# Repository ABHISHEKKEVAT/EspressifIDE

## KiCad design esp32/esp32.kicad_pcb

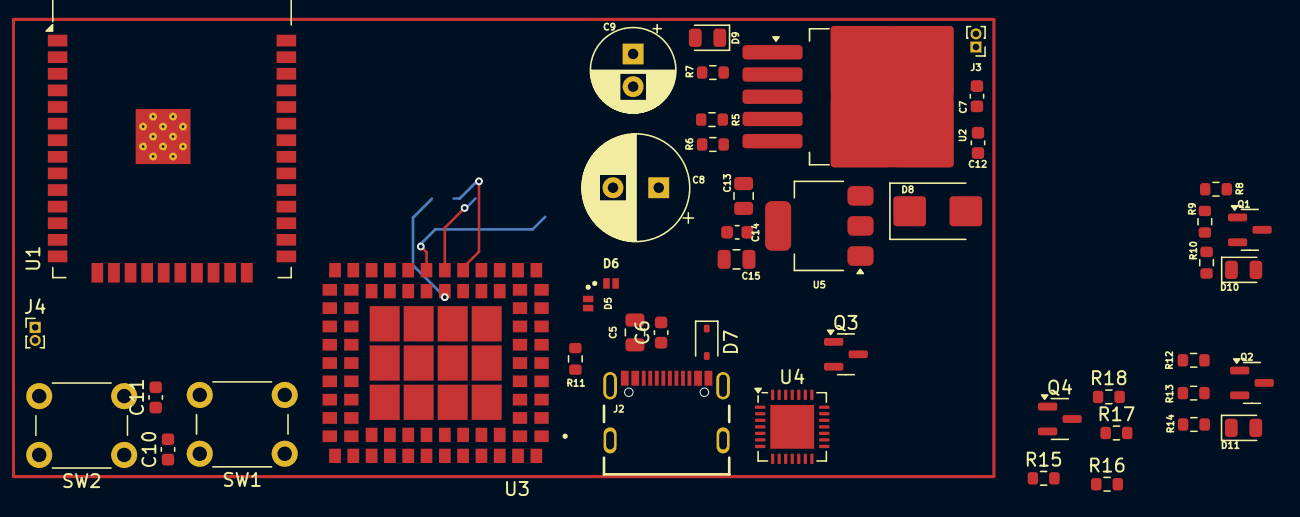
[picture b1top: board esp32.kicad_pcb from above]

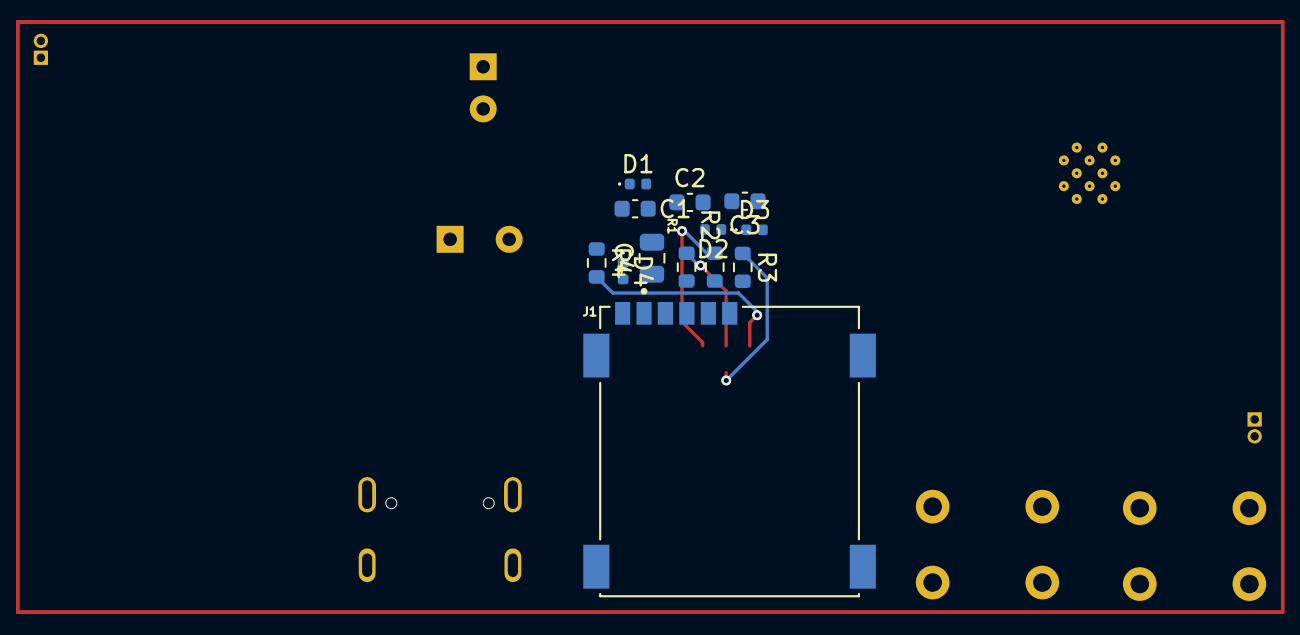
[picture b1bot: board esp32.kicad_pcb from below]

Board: 2 copper layers, 59 parts (13 on the bottom side), 44 nets.

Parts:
C1, C2, C3: 8.2p; C_0603_1608Metric
C4, C5: 1u; C_0805_2012Metric
C6: 22p; C_0603_1608Metric
C7, C12, C14: 100n; C_0603_1608Metric
C8: 100u; CP_Radial_D8.0mm_P3.50mm
C9: 22u; CP_Radial_D6.3mm_P2.50mm
C10, C11: 0.1UF/50V; C_0603_1608Metric
C13, C15: 10u; C_0805_2012Metric
D1, D2, D3, D4: SPD9103W; D_0402_1005Metric
D5, D6: AQ3045-01ETG; DIO_PESD5V0S1UL,315
D7: PESD24VL1BA; D_SOD-323
D8: SS34; D_SMB
D9: PWR; LED_0805_2012Metric
D10: NET; LED_0805_2012Metric
D11: STATUS; LED_0805_2012Metric
J1: SIM7200-6-0-18-00-X_REVA; CUI_MSIM-2-A
J2: USB4105-GF-A; GCT_USB4105-GF-A
J3: PWR; PinHeader_1x02_P1.00mm_Vertical
J4: Conn_01x02; PinHeader_1x02_P1.00mm_Vertical
Q1, Q2, Q3, Q4: BC847; SOT-23
R1, R2, R3: 20R; R_0603_1608Metric
R4, R8, R12: 4.7K; R_0603_1608Metric
R5: 10K; R_0603_1608Metric
R6: 4K7; R_0603_1608Metric
R7, R10, R14: 470R; R_0603_1608Metric
R9, R13: 47K; R_0603_1608Metric
R11: 1K5; R_0603_1608Metric
R15, R16, R17, R18: 0R; R_0603_1608Metric
SW1, SW2: SW_Push; SW_PUSH_6mm_H5mm
U1: ESP32-WROOM-32
U2: MIC29302WU; TO-263-5_TabPin3
U3: SIM800L; MODULE_SIM800L
U4: CP2102N-Axx-xQFN28; QFN-28-1EP_5x5mm_P0.5mm_EP3.35x3.35mm
U5: LM1117MP-3.3; SOT-223-3_TabPin2

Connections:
+3.3V: C14.1, C15.1, U1.2 (VDD), U5.2 (VO)
/esp32/DTR: Q4.3 (C), R17.1, U4.28 (~DTR)
/esp32/EN: Q3.3 (C), U1.3 (EN)
/esp32/IO0: Q4.2 (E), U1.25 (IO0)
/esp32/RTS: Q3.2 (E), R18.1, U4.24 (~RTS)
/esp32/RXD: R15.1, U4.25 (RXD)
/esp32/RXD0: R16.2, U1.34 (RXD0/IO3)
/esp32/TXD: R16.1, U4.26 (TXD)
/esp32/TXD0: R15.2, U1.35 (TXD0/IO1)
/esp32/USB_DM: J2.A7 (DN1), J2.B7 (DN2), U4.4 (D+)
/esp32/USB_DP: J2.A6 (DP1), J2.B6 (DP2), U4.5 (D-)
/usb and sim/EN: C10.2, SW1.2
/usb and sim/IO0: C11.2, SW2.2
/usb and sim/NETLIGHT: R8.1, U3.64 (NETLIGHT)
/usb and sim/SIM1_CLK: R3.1, U3.55 (SIM_CLK)
/usb and sim/SIM1_DATA: R2.1, U3.14 (SIM_DATA)
/usb and sim/SIM1_RESET: J4.1, U3.49 (RESET)
/usb and sim/SIM1_RST: R1.1, U3.15 (SIM_RST), U3.54 (SIM_DET)
/usb and sim/SIM1_VDD: C4.1, D4.2 (A2), J1.C1 (VCC), R4.2, U3.16 (SIM_VDD)
/usb and sim/STATUS: R12.1, U3.4 (STATUS)
/usb and sim/VBAT: D10.2 (A), D11.2 (A)
/usb and sim/VBUS: U3.1 (VBAT), U3.42 (VBAT), U3.56 (VRTC)
GND: C5.2, C6.2, C7.2, C8.2, C9.2, C10.1, C11.1, C12.2, C13.2, C14.2, C15.2, D7.1 (A1), J1.C5 (GND), J2.A1_B12 (GND), J2.B1_A12 (GND), J2.S1 (SHELL_GND), J2.S2 (SHELL_GND), J2.S3 (SHELL_GND), J2.S4 (SHELL_GND), J3.2, J4.2, Q1.2 (E), Q2.2 (E), R6.2, R7.2, R9.2, R11.1, R13.2, SW1.1, SW2.1, U1.1 (GND), U1.15 (GND), U1.38 (GND), U1.39 (GND), U2.3 (GND), U3.2 (GND), U3.6 (GND), U3.8 (GND), U3.35 (GND), U3.37 (GND), U3.38 (GND), U3.39 (GND), U3.41 (GND), U3.43 (GND), U3.44 (GND), U3.45 (GND), U3.58 (GND), U3.67 (GND), U3.71 (GND), U3.72 (GND), U3.73 (GND), U3.76 (GND), U3.77 (GND), U3.78 (GND), U3.79 (GND), U3.80 (GND), U3.81 (GND), U3.82 (GND), U3.83 (GND), U3.84 (GND), U3.85 (GND), U3.86 (GND), U3.87 (GND), U3.88 (GND), U4.3 (GND), U4.29 (GND), U5.1 (GND)
unnamed: C1.2, C2.2, C3.2, C4.2, D1.1 (A1), D2.1 (A1), D3.1 (A1), D4.1 (A1)
unnamed: C1.1, D1.2 (A2), J1.C2 (RST), R1.2
unnamed: C2.1, D2.2 (A2), J1.C7 (I/O), R2.2, R4.1
unnamed: C3.1, D3.2 (A2), J1.C3 (CLK), R3.2
unnamed: D8.2 (A), J3.1
unnamed: C7.1, C8.1, D8.1 (K), U2.1 (EN), U2.2 (VIN)
unnamed: D9.1 (K), R7.1
unnamed: D10.1 (K), R10.2
unnamed: D11.1 (K), R14.2
unnamed: Q1.1 (B), R8.2, R9.1
unnamed: Q1.3 (C), R10.1
unnamed: Q2.1 (B), R12.2, R13.1
unnamed: Q2.3 (C), R14.1
unnamed: Q3.1 (B), R17.2
unnamed: Q4.1 (B), R18.2
unnamed: R5.2, R6.1, U2.5 (ADJ)
unnamed: R11.2, U3.48 (PWRKEY)
SIM1_RXD: U1.28 (IO17), U3.32 (TXD)
SIM1_TXD: U1.27 (IO16), U3.31 (RXD)
VBAT: C9.1, C12.1, C13.1, D9.2 (A), R5.1, U2.4 (VOUT), U4.6 (VDD), U5.3 (VI)
VBUS: C5.1, C6.1, D7.2 (A2), J2.A4_B9 (VBUS), J2.B4_A9 (VBUS), U4.8 (VBUS)

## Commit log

2024-08-05 espressif
2024-08-13 basicauthdone
2024-08-13 okay
2024-08-22 22-08-24
